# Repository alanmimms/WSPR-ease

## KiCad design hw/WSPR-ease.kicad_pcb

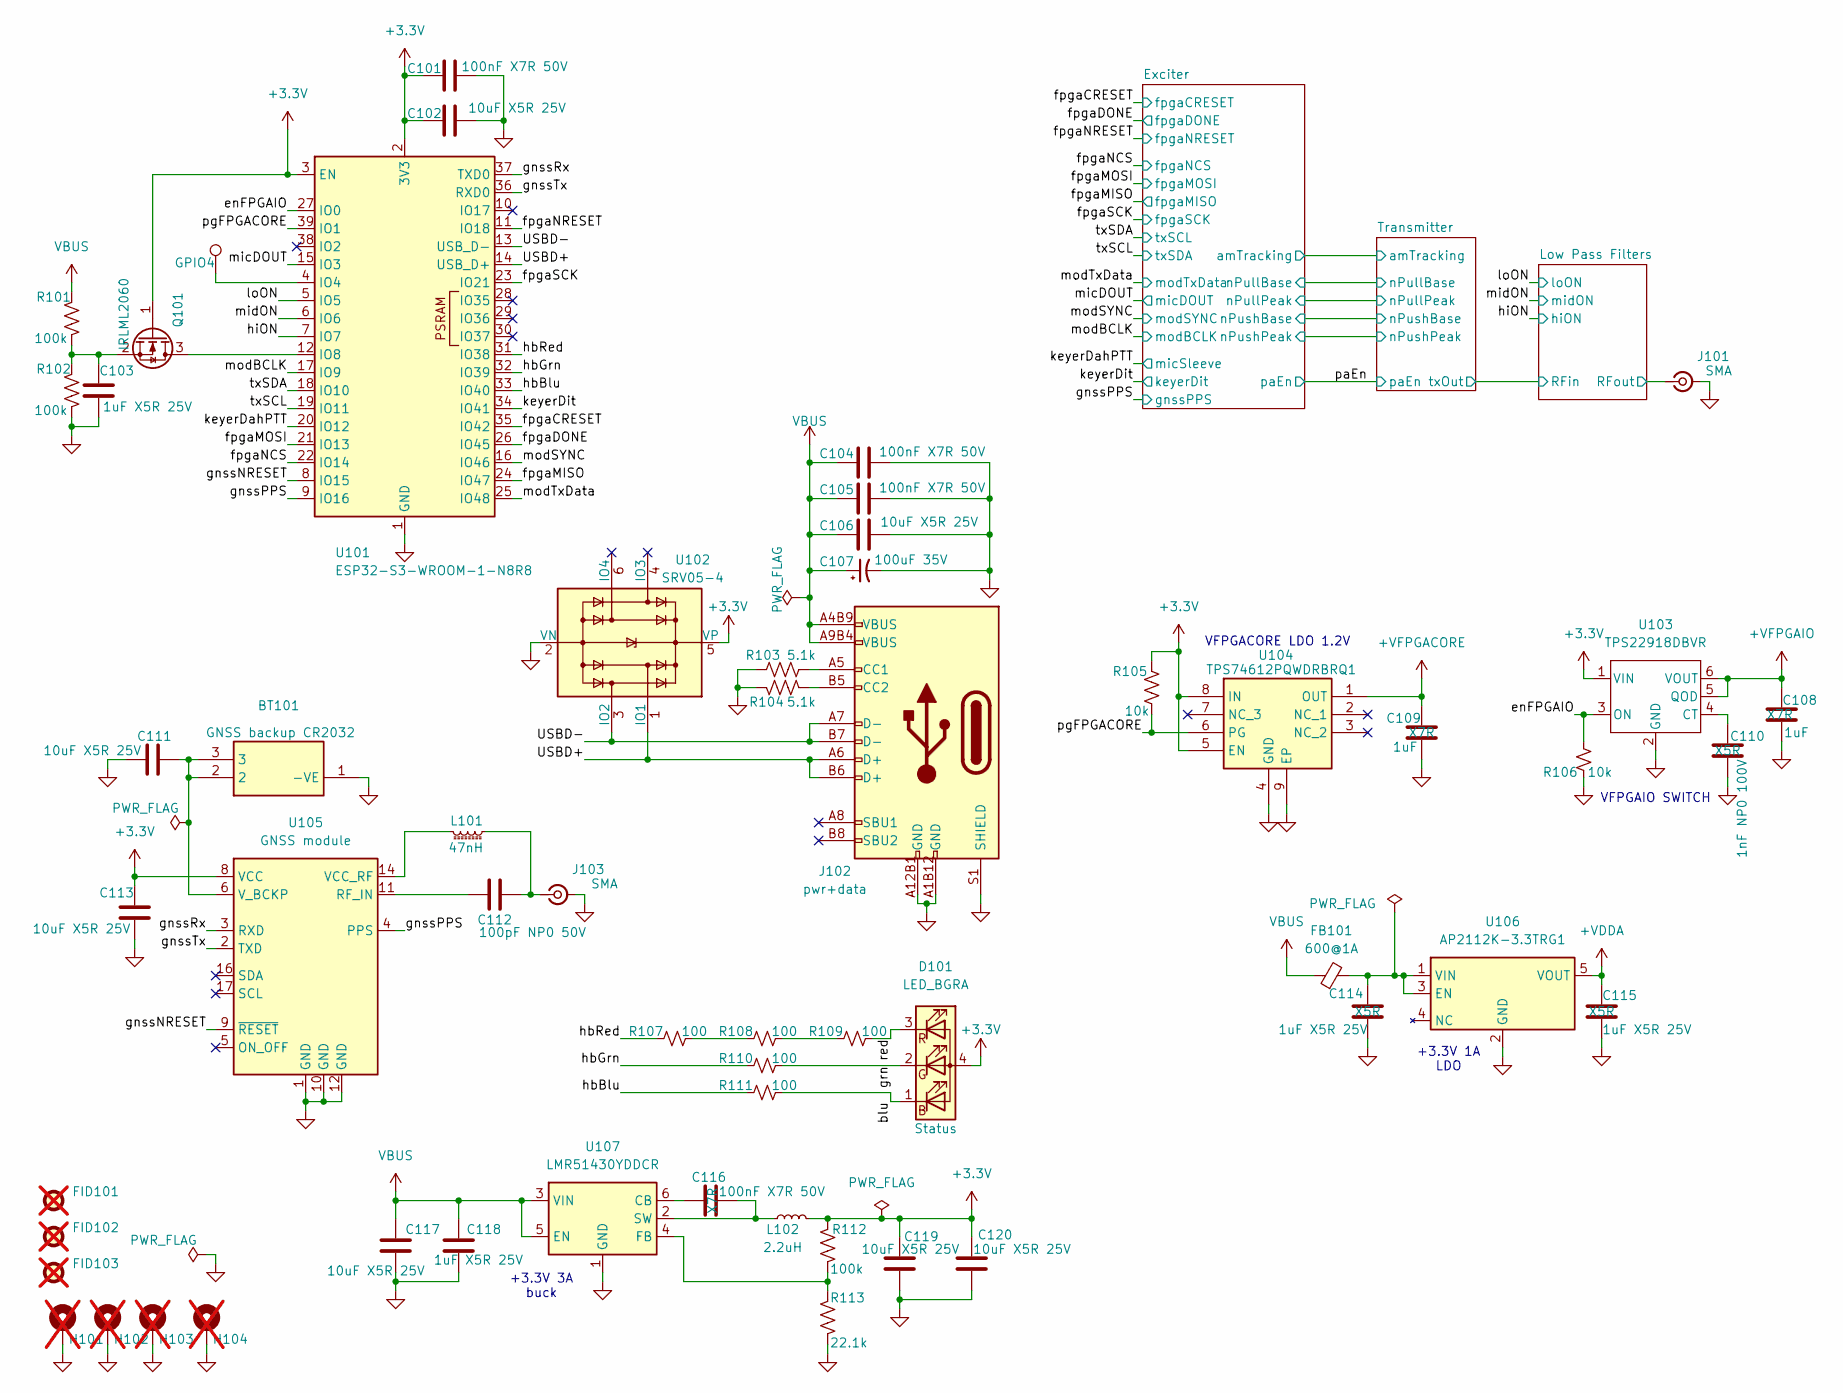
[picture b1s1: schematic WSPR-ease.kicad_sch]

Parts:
BT101: CR3032 holder; S8401-46; Mouser Part Number 855-S8401-46; LCSC C5904513
C101, C104, C105, C116: 100nF X7R 50V; C_0402_1005Metric; MPN KAM05FR71H104KH
C102, C106, C111, C113: 10uF X5R 25V; C_0603_1608Metric; MPN CM105X5R106M25AT; LCSC C479655
C103: 1uF X5R 25V; C_0402_1005Metric; MPN 04023D105MAT2A; LCSC C7393852
C107: 100uF 35V; C_Elec_6.3x7.7; MPN HHXJ350ARA101MF80G; LCSC C46528074
C108, C109: 1uF; C_0402_1005Metric; MPN GRM155Z71A105KE1D; LCSC_PN C301928
C110: 1nF NP0 100V; C_0603_1608Metric; MPN KGM15ACG2A102FT; LCSC_PN C301928
C112: 100pF NP0 50V; C_0402_1005Metric
C114, C115, C118: 1uF X5R 25V; C_0402_1005Metric; MPN 04023D105MAT2A; Mouser_PN 581-04023D105MAT2A
C117: 10uF X5R 25V; C_0603_1608Metric; MPN CM105X5R106M25AT; Mouser_PN 346-CM105X5R106M25AT
C119, C120: 10uF X5R 25V; C_0603_1608Metric; Manufacturer_Part_Number 81-GXT155R71E223KE1D; Mouser Part Number 963-MLAST168BB5106MT
D101: LED_BGRA; UHD111AFKAC3K23E1L3VG5ZB3Z3; MPN UHD111A-FKA-C3K23E1L3VG5ZB3Z3; Mouser_PN 941-UHD1AA3K3E3V53Z3
FB101: 600@1A; L_0603_1608Metric; MPN ILHB0603ER601VHC41; MouserPN 71-ILHB0603E601VHC41
FID101, FID102, FID103: Fiducial; Fiducial_1mm_Mask2mm; LCSC DNP; not fitted
H101, H102, H103, H104: MountingHole_Pad; MountingHole_3.2mm_M3_ISO7380_Pad; LCSC DNP; not fitted
J101, J103: SMA; SMA_Amphenol_901-143_Horizontal; MPN SMA-J-P-H-RA-TH1; LCSC C496551
J102: pwr+data; UJ20-C-H-G-SMT-P16-TR; MPN UJ20-C-H-G-SMT-P16-TR; Mouser_PN 179-UJ20CHGSMTP16TR
L101: 47nH; L_0603_1608Metric; MPN AIMC-0603-47NJ-T; LCSC C98076
L102: 2.2uH; L_1008_2520Metric; MPN APH252010T2R2M; LCSC C5349606
Q101: IRLML2060; SOT-23; MPN IRLML2060TRPBF; Mouser_PN 942-IRLML2060TRPBF
R101, R102: 100k; R_0402_1005Metric; MPN AC0402FR-0747RL; LCSC C2479306
R103, R104: 5.1k; R_0402_1005Metric; MPN MCS04020C5101FE000; Mouser_PN 594-MCS04020C5101FE0
R105: 10k; R_0402_1005Metric; MPN CRT0402-FZ-1003GLF; LCSC_PN C728576
R106: 10k; R_0402_1005Metric; MPN CRT0402-FZ-1003GLF; Mouser_PN 652-CRT0402FZ1003GLF
R107, R108, R109, R110, R111: 100; R_0402_1005Metric; MPN RT0402FRD0722K1L; Mouser_PN 603-RT0402FRD0722K1L
R112: 100k; R_0402_1005Metric; MPN AC0402FR-0747RL; Mouser_PN 603-AC0402FR-0747RL
R113: 22.1k; R_0402_1005Metric; MPN RT0402FRD0722K1L; Mouser_PN 603-RT0402FRD0722K1L
TP101: GPIO4; TestPoint_Pad_1.5x1.5mm
U101: ESP32-S3-WROOM-1-N8R8; ESP32-S3-WROOM-1; Mouser Part Number ESP32-S3-WROOM-1-N8R8; LCSC C2913201
U102: SRV05-4; SOT-23-6; MPN SRV05-4.TCT; LCSC C2836319
U103: TPS22918DBVR; DBV6_TEX; MPN TPS22918DBVR; LCSC_PN C131941
U104: TPS74612PQWDRBRQ1; SON65P300X300X100-9N-D; MPN TPS74612PQWDRBRQ1; LCSC_PN C2868254
U105: GNSS module; ublox_MAX; MPN TESEO-LIV3R; LCSC C5117921
U106: AP2112K-3.3TRG1; SOT95P285X140-5N; Mouser Part Number 621-AP2112K-3.3TRG1
U107: LMR51430YDDCR; SOT-23-6; MPN LMR51430YDDCR; Mouser_PN 595-LMR51430YDDCR

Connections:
+3.3V: C101.1, C102.1, C113.1, C119.1, C120.1, D101.4 (A), L102.2, Q101.1 (G), R105.2, R112.2, U101.2 (3V3), U101.3 (EN), U102.5 (VP), U103.1 (VIN), U104.5 (EN), U104.8 (IN), U105.8 (VCC); also elsewhere on the board
+VDDA: C115.1, U106.5 (VOUT); also elsewhere on the board
+VFPGACORE: C109.1, U104.1 (OUT); also elsewhere on the board
+VFPGAIO: C108.1, U103.5 (QOD), U103.6 (VOUT); also elsewhere on the board
/Low Pass Filters/RFout: J101.1 (In); also elsewhere on the board
/USBD+: J102.A6 (D+), J102.B6 (D+), U101.14 (USB_D+), U102.1 (IO1)
/USBD-: J102.A7 (D-), J102.B7 (D-), U101.13 (USB_D-), U102.3 (IO2)
/blu: D101.1 (BK), R111.2
/enFPGAIO: R106.2, U101.27 (IO0), U103.3 (ON)
/fpgaCRESET: U101.35 (IO42); also elsewhere on the board
/fpgaDONE: U101.26 (IO45); also elsewhere on the board
/fpgaMISO: U101.24 (IO47); also elsewhere on the board
/fpgaMOSI: U101.21 (IO13); also elsewhere on the board
/fpgaNCS: U101.22 (IO14); also elsewhere on the board
/fpgaNRESET: U101.11 (IO18); also elsewhere on the board
/fpgaSCK: U101.23 (IO21); also elsewhere on the board
/gnssNRESET: U101.8 (IO15), U105.9 (~RESET)
/gnssPPS: U101.9 (IO16), U105.4 (PPS); also elsewhere on the board
/gnssRx: U101.37 (TXD0), U105.3 (RXD)
/gnssTx: U101.36 (RXD0), U105.2 (TXD)
/grn: D101.2 (GK), R110.2
/hbBlu: R111.1, U101.33 (IO40)
/hbGrn: R110.1, U101.32 (IO39)
/hbRed: R107.1, U101.31 (IO38)
/hiON: U101.7 (IO7); also elsewhere on the board
/keyerDahPTT: U101.20 (IO12); also elsewhere on the board
/keyerDit: U101.34 (IO41); also elsewhere on the board
/loON: U101.5 (IO5); also elsewhere on the board
/micDOUT: U101.15 (IO3); also elsewhere on the board
/midON: U101.6 (IO6); also elsewhere on the board
/modBCLK: U101.17 (IO9); also elsewhere on the board
/modSYNC: U101.16 (IO46); also elsewhere on the board
/modTxData: U101.25 (IO48); also elsewhere on the board
/pgFPGACORE: R105.1, U101.39 (IO1), U104.6 (PG)
/red: D101.3 (RK), R109.2
/txSCL: U101.19 (IO11); also elsewhere on the board
/txSDA: U101.18 (IO10); also elsewhere on the board
GND: BT101.1 (-VE), C101.2, C102.2, C103.2, C104.2, C105.2, C106.2, C107.2, C108.2, C109.2, C110.2, C111.1, C113.2, C114.2, C115.2, C117.2, C118.2, C119.2, C120.2, H101.1, H102.1, H103.1, H104.1, J101.2 (Ext), J102.A1B12 (GND), J102.A12B1 (GND), J102.S1 (SHIELD), J103.2 (Ext), R102.2, R103.2, R104.2, R106.1, R113.1, U101.1 (GND), U101.40 (GND), U101.41 (GND), U102.2 (VN), U103.2 (GND), U104.4 (GND), U104.9 (EP), U105.1 (GND), U105.10 (GND), U105.12 (GND), U106.2 (GND), U107.1 (GND); also elsewhere on the board
unnamed: J102.A5 (CC1), R103.1
unnamed: J102.B5 (CC2), R104.1
unnamed: C112.2, J103.1 (In), L101.2
unnamed: Q101.3 (D), U101.12 (IO8)
unnamed: C103.1, Q101.2 (S), R101.2, R102.1
unnamed: R107.2, R108.1
unnamed: R108.2, R109.1
unnamed: TP101.1, U101.4 (IO4)
unnamed: C110.1, U103.4 (CT)
unnamed: C112.1, U105.11 (RF_IN)
unnamed: L101.1, U105.14 (VCC_RF)
unnamed: BT101.2, BT101.3, C111.2, U105.6 (V_BCKP)
unnamed: C114.1, FB101.2, U106.1 (VIN), U106.3 (EN)
unnamed: C116.1, U107.6 (CB)
unnamed: R112.1, R113.2, U107.4 (FB)
unnamed: C116.2, L102.1, U107.2 (SW)
VBUS: C104.1, C105.1, C106.1, C107.1, C117.1, C118.1, FB101.1, J102.A4B9 (VBUS), J102.A9B4 (VBUS), R101.1, U107.3 (VIN), U107.5 (EN); also elsewhere on the board

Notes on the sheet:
VFPGAIO SWITCH
+3.3V 1A LDO
+3.3V 3A buck
VFPGACORE LDO 1.2V

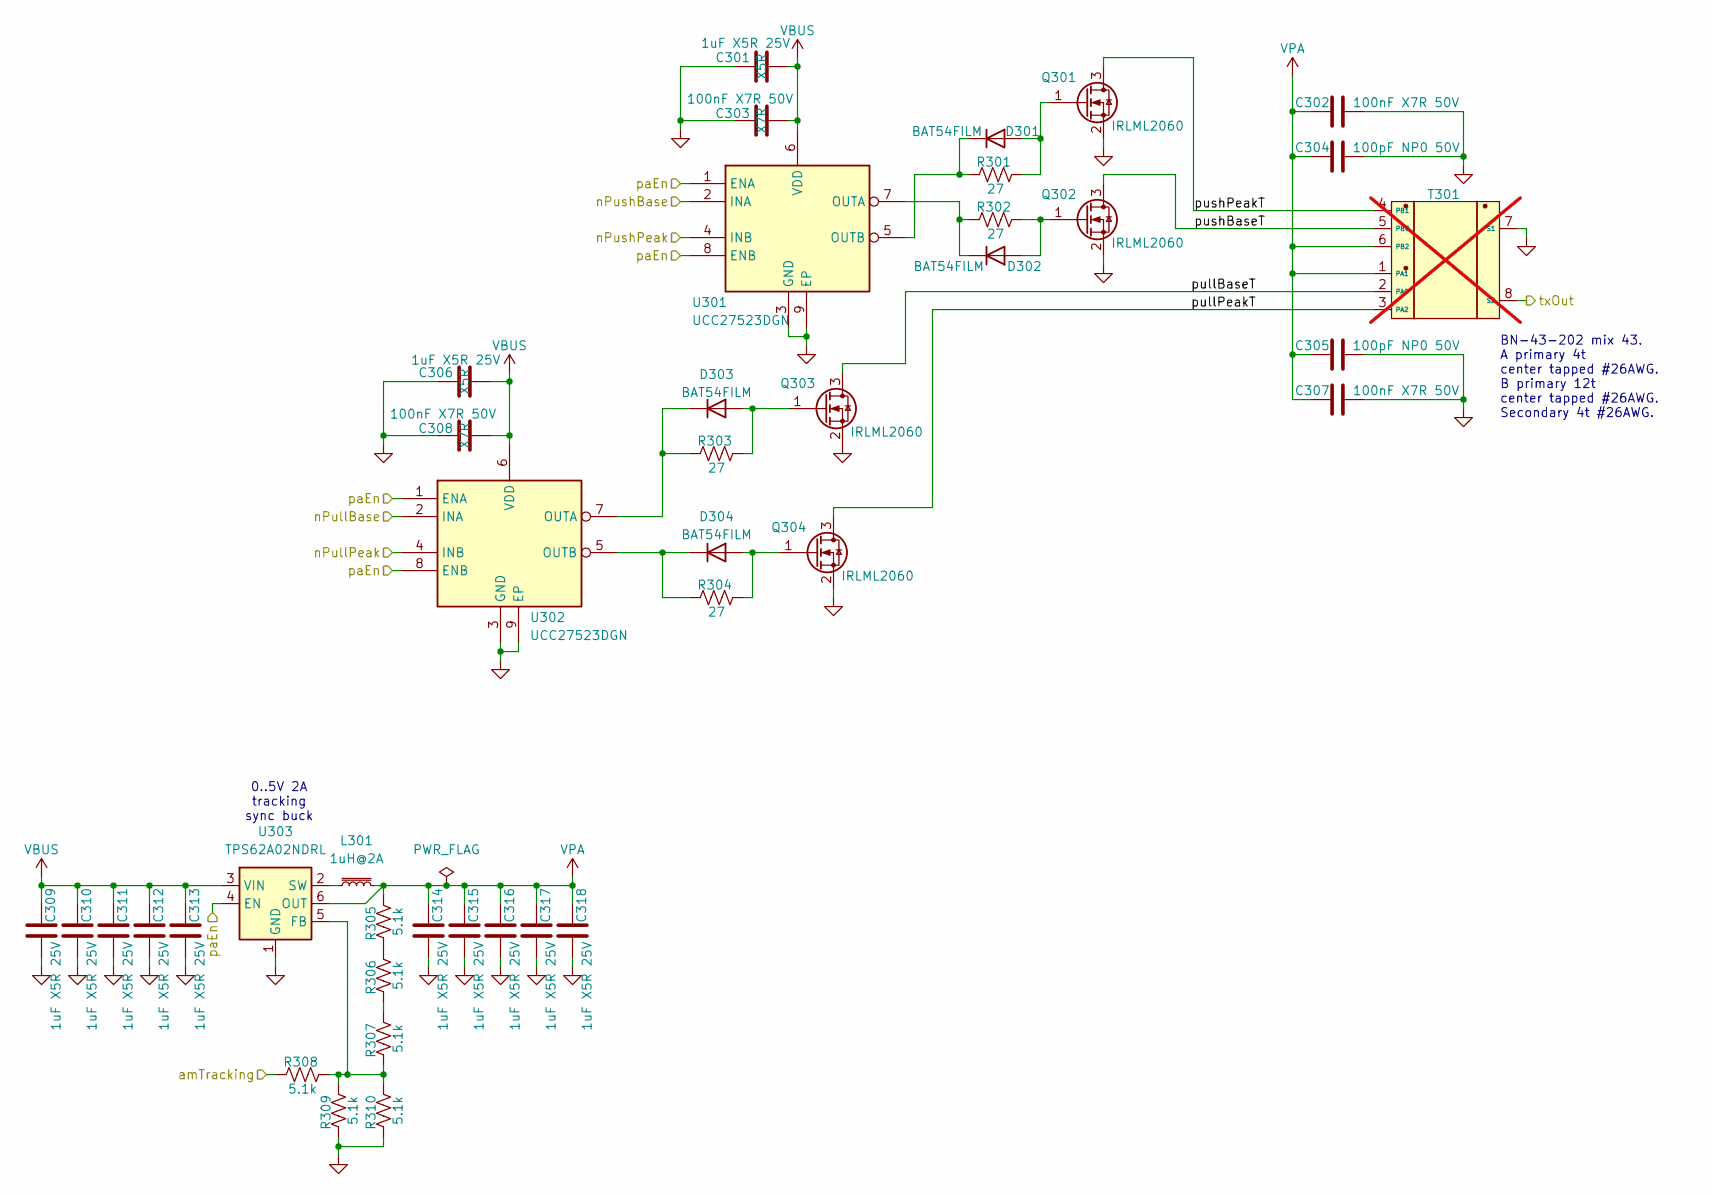
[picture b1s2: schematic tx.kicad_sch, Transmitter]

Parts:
C301, C306: 1uF X5R 25V; C_0402_1005Metric; MPN 04023D105MAT2A; Mouser_PN 581-04023D105MAT2A
C302, C303, C307, C308: 100nF X7R 50V; C_0402_1005Metric; MPN KAM05FR71H104KH
C304, C305: 100pF NP0 50V; C_0402_1005Metric
C309, C310, C311, C312, C313, C314, C315, C316, C317, C318: 1uF X5R 25V; C_0402_1005Metric; MPN 04023D105MAT2A; LCSC C7393852
D301, D302, D303, D304: BAT54FILM; D_SOD-123; MPN BAT54ZFILM; Mouser_PN 511-BAT54FILM
L301: 1uH@2A; PFL4514-inductor; MPN PFL4514-102MEC
Q301, Q302, Q303, Q304: IRLML2060; SOT-23; MPN IRLML2060TRPBF; Mouser_PN 942-IRLML2060TRPBF
R301, R302, R303, R304: 27; R_0402_1005Metric; MPN MCS04020C5101FE000; LCSC C2906874
R305, R306, R307, R308, R309, R310: 5.1k; R_0402_1005Metric
T301: BN-43-202_DualPri_CTSec; bn-43-202-horizontal; MPN 2843000202; LCSC C7174817; not fitted
U301, U302: UCC27523DGN; SOP65P490X110-9N; MPN UCC27525DGNR; Mouser_PN 595-UCC27525DGNR
U303: TPS62A02NDRL; SOT-563

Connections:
/Exciter/amTracking: R308.1; also elsewhere on the board
/Exciter/nPullBase: U302.2 (INA); also elsewhere on the board
/Exciter/nPullPeak: U302.4 (INB); also elsewhere on the board
/Exciter/nPushBase: U301.2 (INA); also elsewhere on the board
/Exciter/nPushPeak: U301.4 (INB); also elsewhere on the board
/Low Pass Filters/RFin: T301.8 (S2); also elsewhere on the board
/Transmitter/pullBaseT: Q303.3 (D), T301.2 (PAC)
/Transmitter/pullPeakT: Q304.3 (D), T301.3 (PA2)
/Transmitter/pushBaseT: Q302.3 (D), T301.5 (PBC)
/Transmitter/pushPeakT: Q301.3 (D), T301.4 (PB1)
/paEn: U301.1 (ENA), U301.8 (ENB), U302.1 (ENA), U302.8 (ENB), U303.4 (EN); also elsewhere on the board
GND: C301.1, C302.2, C303.1, C304.2, C305.2, C306.1, C307.2, C308.1, C309.2, C310.2, C311.2, C312.2, C313.2, C314.2, C315.2, C316.2, C317.2, C318.2, Q301.2 (S), Q302.2 (S), Q303.2 (S), Q304.2 (S), R309.1, R310.1, T301.7 (S1), U301.3 (GND), U301.9 (EP), U302.3 (GND), U302.9 (EP), U303.1 (GND); also elsewhere on the board
unnamed: D301.2 (A), Q301.1 (G), R301.2
unnamed: D301.1 (K), R301.1, U301.5 (OUTB)
unnamed: D302.2 (A), Q302.1 (G), R302.2
unnamed: D302.1 (K), R302.1, U301.7 (OUTA)
unnamed: D303.2 (A), Q303.1 (G), R303.2
unnamed: D303.1 (K), R303.1, U302.7 (OUTA)
unnamed: D304.2 (A), Q304.1 (G), R304.2
unnamed: D304.1 (K), R304.1, U302.5 (OUTB)
unnamed: R305.1, R306.2
unnamed: R306.1, R307.2
unnamed: R307.1, R308.2, R309.2, R310.2, U303.5 (FB)
unnamed: L301.1, U303.2 (SW)
VBUS: C301.2, C303.2, C306.2, C308.2, C309.1, C310.1, C311.1, C312.1, C313.1, U301.6 (VDD), U302.6 (VDD), U303.3 (VIN); also elsewhere on the board
VPA: C302.1, C304.1, C305.1, C307.1, C314.1, C315.1, C316.1, C317.1, C318.1, L301.2, R305.2, T301.1 (PA1), T301.6 (PB2), U303.6 (OUT)

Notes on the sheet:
BN-43-202 mix 43. A primary 4t center tapped #26AWG. B primary 12t center tapped #26AWG. Secondary 4t #26AWG.
0..5V 2A tracking sync buck

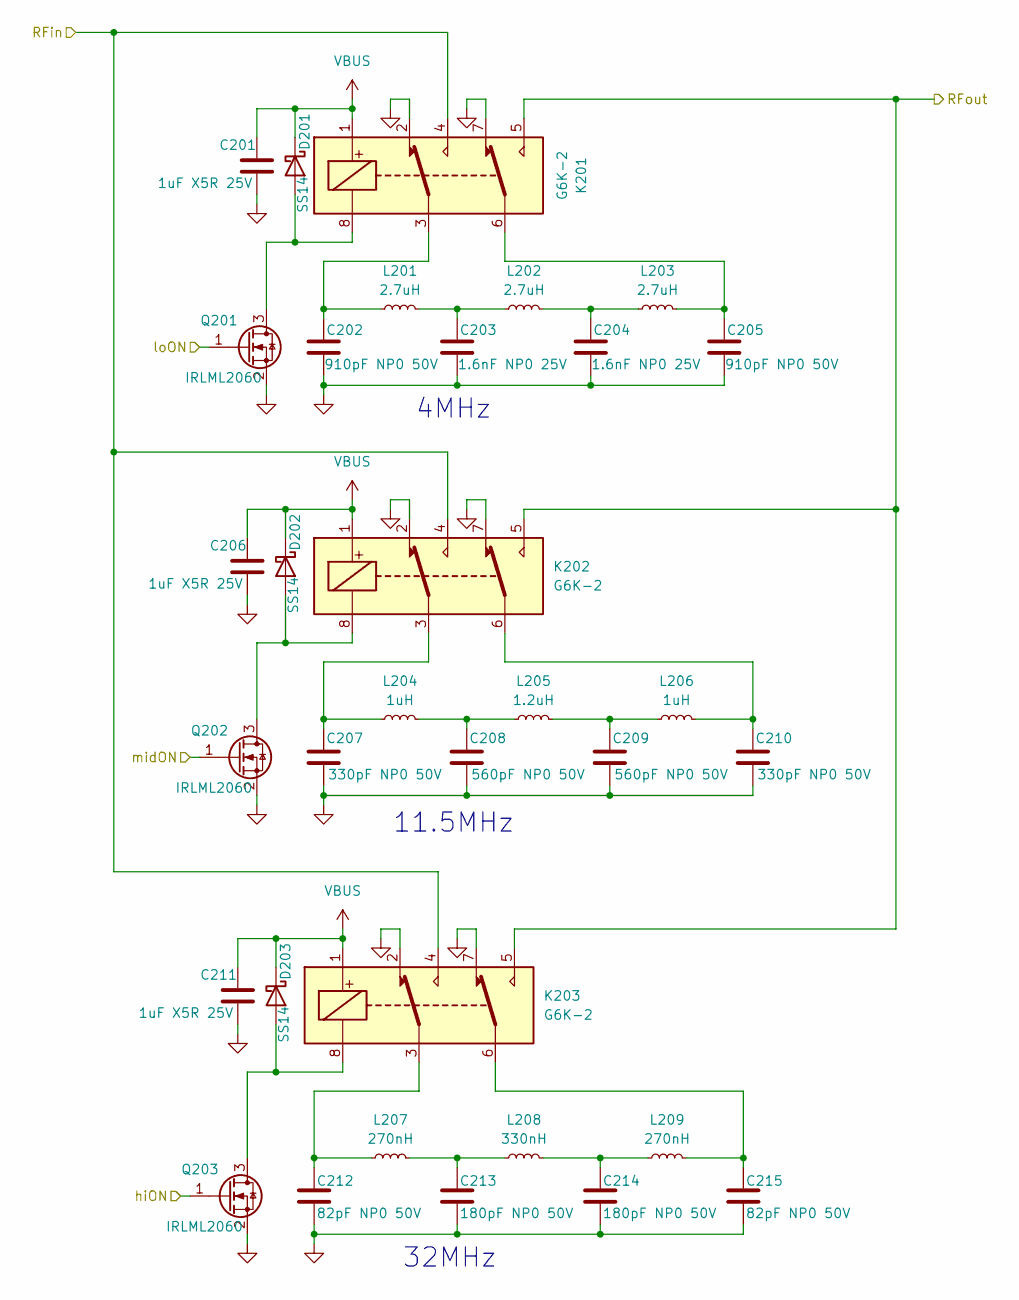
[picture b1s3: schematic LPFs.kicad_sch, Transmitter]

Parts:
C201, C206, C211: 1uF X5R 25V; C_0402_1005Metric; MPN 04023D105MAT2A; LCSC C7393852
C202, C205: 910pF NP0 50V; C_0402_1005Metric
C203, C204: 1.6nF NP0 25V; C_0402_1005Metric
C207, C210: 330pF NP0 50V; C_0402_1005Metric
C208, C209: 560pF NP0 50V; C_0402_1005Metric
C212, C215: 82pF NP0 50V; C_0402_1005Metric
C213, C214: 180pF NP0 50V; C_0402_1005Metric
D201, D202, D203: SS14; D_SMA; MPN SS14; LCSC C45406502
K201, K202, K203: G6K-2; Relay_DPDT_Omron_G6K-2G; MPN G6K-2G-DC5; Mouser_PN 653-G6K-2G-DC5
L201, L202, L203: 2.7uH; L_1008_2520Metric; MPN 1008LS-272XJRC; Mouser_PN 994-1008LS-272XJRC
L204, L206: 1uH; L_1008_2520Metric; MPN 1008CS-102XJRC; Mouser_PN 994-1008CS-102XJRC
L205: 1.2uH; L_1008_2520Metric; MPN 1008CS-122XJRC; Mouser_PN 994-1008CS-122XJRC
L207, L209: 270nH; L_0805_2012Metric; MPN 1008CS-271XGRC; LCSC C48946576
L208: 330nH; L_0805_2012Metric; MPN 1008CS-331XGRC; LCSC C48946577
Q201, Q202, Q203: IRLML2060; SOT-23; MPN IRLML2060TRPBF; Mouser_PN 942-IRLML2060TRPBF

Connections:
/Low Pass Filters/RFin: K201.4, K202.4, K203.4; also elsewhere on the board
/Low Pass Filters/RFout: K201.5, K202.5, K203.5; also elsewhere on the board
/hiON: Q203.1 (G); also elsewhere on the board
/loON: Q201.1 (G); also elsewhere on the board
/midON: Q202.1 (G); also elsewhere on the board
GND: C201.2, C202.2, C203.2, C204.2, C205.2, C206.2, C207.2, C208.2, C209.2, C210.2, C211.2, C212.2, C213.2, C214.2, C215.2, K201.2, K201.7, K202.2, K202.7, K203.2, K203.7, Q201.2 (S), Q202.2 (S), Q203.2 (S); also elsewhere on the board
unnamed: C202.1, K201.3, L201.1
unnamed: C203.1, L201.2, L202.1
unnamed: C204.1, L202.2, L203.1
unnamed: C205.1, K201.6, L203.2
unnamed: C207.1, K202.3, L204.1
unnamed: C208.1, L204.2, L205.1
unnamed: C209.1, L205.2, L206.1
unnamed: C210.1, K202.6, L206.2
unnamed: C212.1, K203.3, L207.1
unnamed: C213.1, L207.2, L208.1
unnamed: C214.1, L208.2, L209.1
unnamed: C215.1, K203.6, L209.2
unnamed: D201.2 (A), K201.8, Q201.3 (D)
unnamed: D202.2 (A), K202.8, Q202.3 (D)
unnamed: D203.2 (A), K203.8, Q203.3 (D)
VBUS: C201.1, C206.1, C211.1, D201.1 (K), D202.1 (K), D203.1 (K), K201.1, K202.1, K203.1; also elsewhere on the board

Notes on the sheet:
4MHz
32MHz
11.5MHz

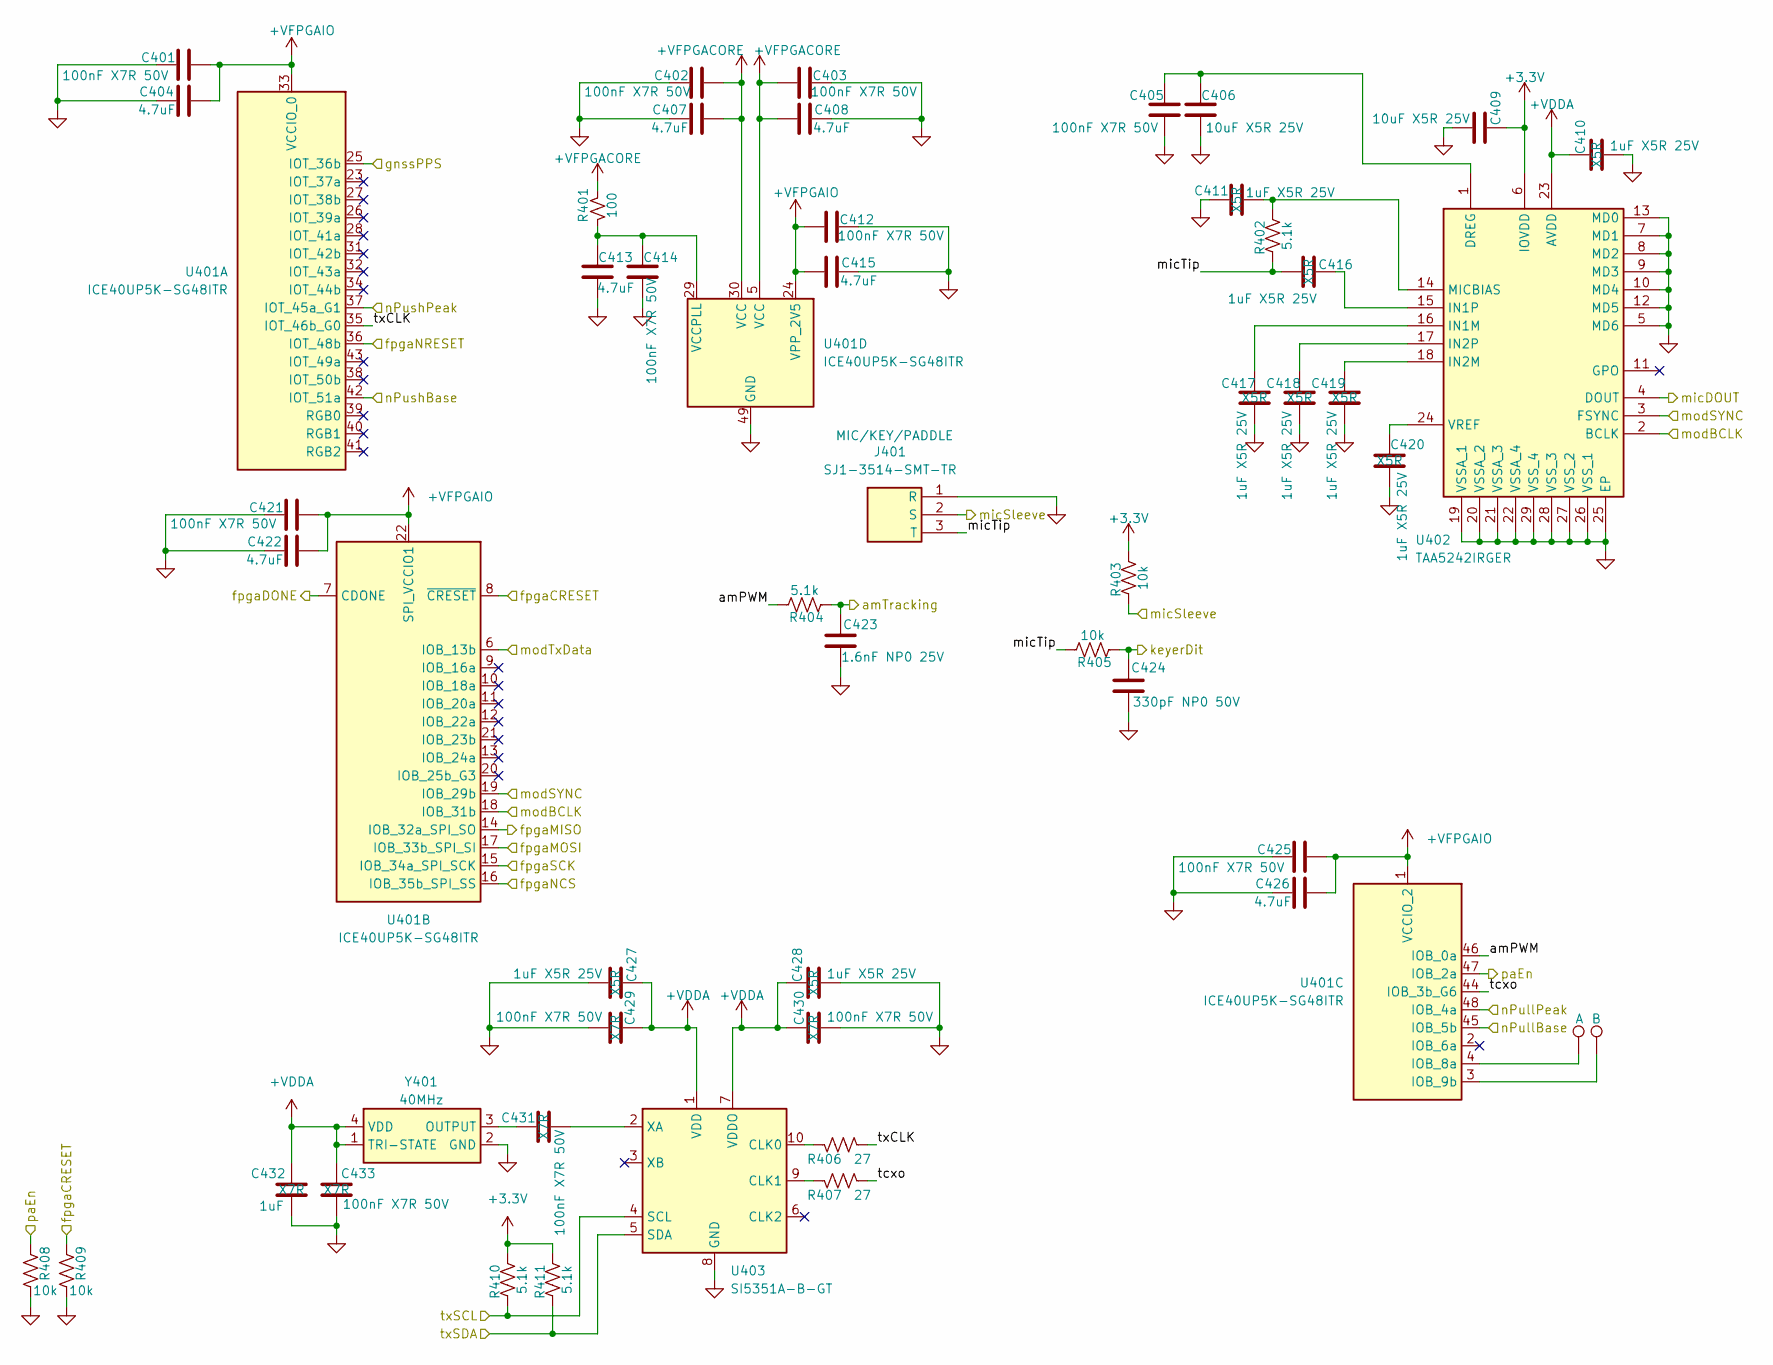
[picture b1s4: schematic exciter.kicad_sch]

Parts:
C401, C402, C403, C405, C412, C414, C421, C425: 100nF X7R 50V; C_0402_1005Metric; MPN KGM15BR71H104KT; LCSC C24452
C404, C407, C408, C413, C415, C422, C426: 4.7uF; C_0402_1005Metric; MPN CM05X5R475M10AH; LCSC_PN C18535241
C406: 10uF X5R 25V; C_0603_1608Metric; Manufacturer_Part_Number 81-GXT155R71E223KE1D; Mouser Part Number 963-MLAST168BB5106MT
C409: 10uF X5R 25V; C_0603_1608Metric; MPN CM105X5R106M25AT; LCSC C96446
C410, C411, C416, C417, C418, C419, C420, C427, C428: 1uF X5R 25V; C_0402_1005Metric; MPN 04023D105MAT2A; Mouser_PN 581-04023D105MAT2A
C423: 1.6nF NP0 25V; C_0402_1005Metric
C424: 330pF NP0 50V; C_0402_1005Metric
C429, C430, C431: 100nF X7R 50V; C_0402_1005Metric; MPN KAM05FR71H104KH
C432: 1uF; C_0402_1005Metric; MPN GRM155Z71A105KE1D; LCSC_PN C301928
C433: 100nF X7R 50V; C_0402_1005Metric; MPN KGM15BR71H104KT; LCSC_PN C24452
J401: SJ1-3514-SMT-TR; 35RASMT2BHWNTRX; Mouser Part Number 502-35RASMT2BHWNTRX
R401: 100; R_0402_1005Metric; MPN RT0402FRD0722K1L; Mouser_PN 603-RT0402FRD0722K1L
R402, R404: 5.1k; R_0402_1005Metric; MPN MCT06030C1009FP500; LCSC C2907091
R403, R405: 10k; R_0402_1005Metric; MPN MCT06030C1009FP500; LCSC C2907091
R406, R407: 27; R_0402_1005Metric; MPN MCS04020C5101FE000; Mouser_PN 594-MCS04020C5101FE0
R408, R409: 10k; R_0402_1005Metric; MPN CRT0402-FZ-1003GLF; LCSC C60490
R410, R411: 5.1k; R_0402_1005Metric; MPN MCS04020C5101FE000; LCSC C2906874
TP401: A; TestPoint_Pad_1.5x1.5mm
TP402: B; TestPoint_Pad_1.5x1.5mm
U401: ICE40UP5K-SG48ITR; QFN50P700X700X100-49N-D; MPN ICE40UP5K-SG48I; LCSC C2678152
U402: TAA5242IRGER; Manufacturer_Part_Number TAA5242IRGER
U403: SI5351A-B-GT; MSOP-10_3x3mm_P0.5mm; MPN SI5351C-B-GM1; Mouser_PN 634-SI5351C-B-GM1
Y401: 40MHz; ECSTXO201633400TR; MPN ECS-TXO-2016-33-400-TR; LCSC_PN C2451471

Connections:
+3.3V: C409.2, R403.2, R410.2, R411.2, U402.6 (IOVDD); also elsewhere on the board
+VDDA: C410.1, C427.1, C428.1, C429.2, C430.2, C432.1, C433.1, U402.23 (AVDD), U403.1 (VDD), U403.7 (VDDO), Y401.1 (TRI-STATE), Y401.4 (VDD); also elsewhere on the board
+VFPGACORE: C402.2, C403.2, C407.1, C408.1, R401.2, U401.5 (VCC), U401.30 (VCC); also elsewhere on the board
+VFPGAIO: C401.2, C404.1, C412.2, C415.1, C421.2, C422.1, C425.2, C426.1, U401.1 (VCCIO_2), U401.22 (SPI_VCCIO1), U401.24 (VPP_2V5), U401.33 (VCCIO_0); also elsewhere on the board
/Exciter/amPWM: R404.2, U401.46 (IOB_0a)
/Exciter/amTracking: C423.1, R404.1; also elsewhere on the board
/Exciter/micTip: C416.2, J401.3 (T), R402.1, R405.2
/Exciter/nPullBase: U401.45 (IOB_5b); also elsewhere on the board
/Exciter/nPullPeak: U401.48 (IOB_4a); also elsewhere on the board
/Exciter/nPushBase: U401.42 (IOT_51a); also elsewhere on the board
/Exciter/nPushPeak: U401.37 (IOT_45a_G1); also elsewhere on the board
/Exciter/tcxo: R407.1, U401.44 (IOB_3b_G6)
/Exciter/txCLK: R406.1, U401.35 (IOT_46b_G0)
/fpgaCRESET: R409.1, U401.8 (~CRESET); also elsewhere on the board
/fpgaDONE: U401.7 (CDONE); also elsewhere on the board
/fpgaMISO: U401.14 (IOB_32a_SPI_SO); also elsewhere on the board
/fpgaMOSI: U401.17 (IOB_33b_SPI_SI); also elsewhere on the board
/fpgaNCS: U401.16 (IOB_35b_SPI_SS); also elsewhere on the board
/fpgaNRESET: U401.36 (IOT_48b); also elsewhere on the board
/fpgaSCK: U401.15 (IOB_34a_SPI_SCK); also elsewhere on the board
/gnssPPS: U401.25 (IOT_36b); also elsewhere on the board
/keyerDahPTT: J401.2 (S), R403.1; also elsewhere on the board
/keyerDit: C424.1, R405.1; also elsewhere on the board
/micDOUT: U402.4 (DOUT); also elsewhere on the board
/modBCLK: U401.18 (IOB_31b), U402.2 (BCLK); also elsewhere on the board
/modSYNC: U401.19 (IOB_29b), U402.3 (FSYNC); also elsewhere on the board
/modTxData: U401.6 (IOB_13b); also elsewhere on the board
/paEn: R408.1, U401.47 (IOB_2a); also elsewhere on the board
/txSCL: R411.1, U403.5 (SDA); also elsewhere on the board
/txSDA: R410.1, U403.4 (SCL); also elsewhere on the board
GND: C401.1, C402.1, C403.1, C404.2, C405.1, C406.1, C407.2, C408.2, C409.1, C410.2, C411.2, C412.1, C413.2, C414.1, C415.2, C417.2, C418.2, C419.2, C420.2, C421.1, C422.2, C423.2, C424.2, C425.1, C426.2, C427.2, C428.2, C429.1, C430.1, C432.2, C433.2, J401.1 (R), R408.2, R409.2, U401.49 (GND), U402.5 (MD6), U402.7 (MD1), U402.8 (MD2), U402.9 (MD3), U402.10 (MD4), U402.12 (MD5), U402.13 (MD0), U402.19 (VSSA_1), U402.20 (VSSA_2), U402.21 (VSSA_3), U402.22 (VSSA_4), U402.25 (EP), U402.26 (VSS_1), U402.27 (VSS_2), U402.28 (VSS_3), U402.29 (VSS_4), U403.8 (GND), Y401.2 (GND); also elsewhere on the board
unnamed: TP401.1, U401.4 (IOB_8a)
unnamed: TP402.1, U401.3 (IOB_9b)
unnamed: C413.1, C414.2, R401.1, U401.29 (VCCPLL)
unnamed: C405.2, C406.2, U402.1 (DREG)
unnamed: C417.1, U402.16 (IN1M)
unnamed: C416.1, U402.15 (IN1P)
unnamed: C419.1, U402.18 (IN2M)
unnamed: C418.1, U402.17 (IN2P)
unnamed: C411.1, R402.2, U402.14 (MICBIAS)
unnamed: C420.1, U402.24 (VREF)
unnamed: R406.2, U403.10 (CLK0)
unnamed: R407.2, U403.9 (CLK1)
unnamed: C431.2, U403.2 (XA)
unnamed: C431.1, Y401.3 (OUTPUT)

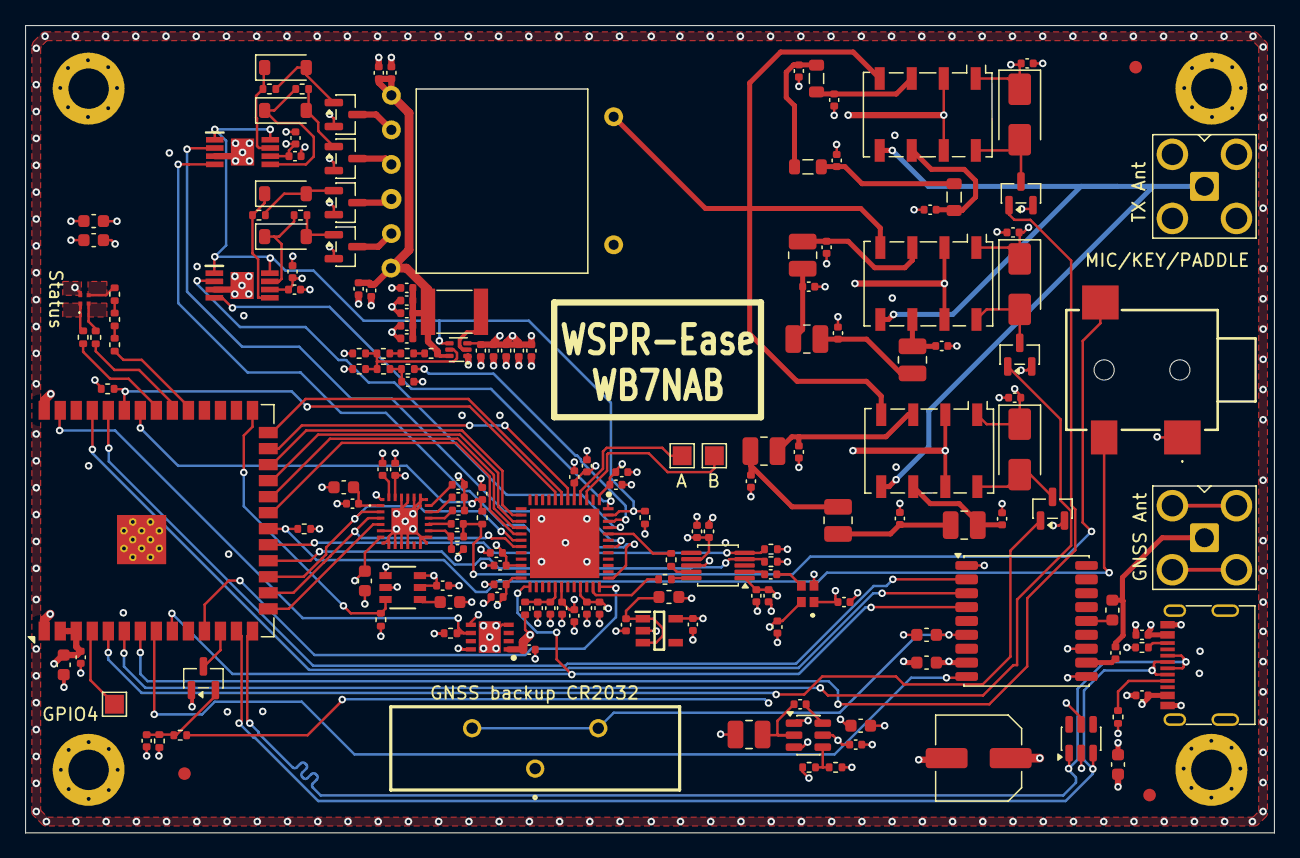
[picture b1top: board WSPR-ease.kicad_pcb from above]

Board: 4 copper layers, 99.0 x 64.0 mm, 182 parts (0 on the bottom side), 112 nets.

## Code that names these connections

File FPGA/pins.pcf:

# Clock Inputs
set_io txCLK 35
set_io tcxo 44
set_io gnssPPS 25

# SPI Interface
set_io fpgaMISO 14
set_io fpgaSCK 15
set_io fpgaNCS 16
set_io fpgaMOSI 17

# I2S Audio Bus Inputs (from ESP32, BCLK/SYNC shared with mic ADC)
set_io modTxData 6
set_io modBCLK 18
set_io modSYNC 19

# RF Exciter & Control Outputs
set_io rfPushPeak 37
set_io rfPushBase 42
set_io rfPullPeak 48
set_io rfPullBase 45
set_io paEn 47
set_io amPWM 46

# Debug Pads
set_io padA 4
set_io padB 3

# Reset without reconfiguration
set_io fpgaNRESET 36

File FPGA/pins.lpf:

# WSPR-ease CPLD Pin Constraints
# Device: LCMXO2-256HC-4SG32C (32-pin QFN/TQFP)

LOCATE COMP "rf_clk_pin" SITE "21";     # PCLKT1_0 (modulated clock from Si5351 CLK0)
LOCATE COMP "pwm_clk_pin" SITE "4";      # PCLKT3_0 (PWM rate clock from Si5351 CLK2)
LOCATE COMP "pwm_out" SITE "5";          # PCLKC3_0 (PWM output driving RC filter)
LOCATE COMP "nPullPeak" SITE "11";       # PCLKT2_0 (active-low gate output)
LOCATE COMP "nPullBase" SITE "12";       # PCLKC2_0 (active-low gate output)
LOCATE COMP "nPushPeak" SITE "13";       # PCLKT2_1 (active-low gate output)
LOCATE COMP "nPushBase" SITE "14";       # PCLKC2_1 (active-low gate output)
LOCATE COMP "fpgaNCS" SITE "8";          # SPI CS
LOCATE COMP "fpgaMOSI" SITE "17";        # SPI MOSI
LOCATE COMP "fpgaMISO" SITE "10";        # SPI MISO
LOCATE COMP "fpgaSCLKpin" SITE "9";      # SPI SCK (Clock)

IOBUF PORT "rf_clk_pin" IO_TYPE=LVCMOS33PULLMODE=NONE;
IOBUF PORT "pwm_clk_pin" IO_TYPE=LVCMOS33PULLMODE=NONE;
IOBUF PORT "pwm_out" IO_TYPE=LVCMOS33 SLEWRATE=FAST DRIVE=8;
IOBUF PORT "nPullPeak" IO_TYPE=LVCMOS33 SLEWRATE=FAST DRIVE=8;
IOBUF PORT "nPullBase" IO_TYPE=LVCMOS33 SLEWRATE=FAST DRIVE=8;
IOBUF PORT "nPushPeak" IO_TYPE=LVCMOS33 SLEWRATE=FAST DRIVE=8;
IOBUF PORT "nPushBase" IO_TYPE=LVCMOS33 SLEWRATE=FAST DRIVE=8;
IOBUF PORT "fpgaNCS" IO_TYPE=LVCMOS33 PULLMODE=UP;
IOBUF PORT "fpgaMOSI" IO_TYPE=LVCMOS33 PULLMODE=NONE;
IOBUF PORT "fpgaMISO" IO_TYPE=LVCMOS33 SLEWRATE=FAST DRIVE=8;
IOBUF PORT "fpgaSCLKpin" IO_TYPE=LVCMOS33 PULLMODE=NONE;

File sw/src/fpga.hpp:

/*
 * CPLD/FPGA Control Module for WSPR-ease
 * Handles CPLD interaction, Si5351 clock initialization, and SPI register updates.
 */

#pragma once

#include <cstdint>
#include "Si5351.hpp"

namespace wspr {

  enum class WSPRBand : uint32_t {
    Band160m = 1836600,
    Band80m  = 3568600,
    Band60m  = 5287200,
    Band40m  = 7038600,
    Band30m  = 10138700,
    Band20m  = 14095600,
    Band17m  = 18104600,
    Band15m  = 21094600,
    Band12m  = 24924600,
    Band10m  = 28124600,
    Band6m   = 50293000,
  };

  class FPGA {
  public:
    static FPGA& instance();

    static const unsigned tcxoFreqHz = 20 * 1000 * 1000; // 20 MHz TCXO reference for Si5351

    int init();
    int reset();
    int loadBitstream(const char* path);

    // Frequency control (CLK0 outputs 6x this frequency)
    int setFrequency(uint32_t freq_hz);
    uint32_t frequency() const { return currentFreq; }

    // Transmission control
    int startTX();
    int stopTX();
    bool isTransmitting() const { return initialized && transmitting; }

    // Send WSPR symbol (0-3) - 4-FSK modulation
    int sendSymbol(uint8_t symbol);

    // LPF band switching (controlled by loON, midON, hiON GPIOs)
    int setLPFBand(WSPRBand band);
    WSPRBand getBand() const { return currentBand; }

    // Atomic Polar Modulation update for AM, SSB, and CW envelope
    int updatePolarMod(uint16_t amplitude, uint16_t phase);

    // Soft reset trigger for internal CPLD state machines
    int triggerSoftReset(bool assertReset);

    // Raw register access for diagnostics
    int readRegister(uint8_t reg, uint32_t* value) { return spiReadReg(reg, value); }
    int writeRegister(uint8_t reg, uint32_t value) { return spiWriteReg(reg, value); }

    bool isInitialized() const { return initialized; }

    // Reference to Si5351 instance
    Si5351& getSi5351() { return si5351; }

  private:
    FPGA() = default;

    int spiWriteReg(uint8_t reg, uint32_t value);
    int spiReadReg(uint8_t reg, uint32_t* value);

    bool initialized = false;
    bool transmitting = false;
    uint32_t currentFreq = 0;
    WSPRBand currentBand = WSPRBand::Band20m;

    Si5351 si5351;
  };

} // namespace wspr

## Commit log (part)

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2026-04-13 1-2-1 last rites?
2026-04-13 Actually this might be last 1-2-1 version instead
2026-04-16 Use relays and do layout over again to make these damned things fit
2026-04-16 Timing closure at ~87MHz with DSP mutiplier approach and cosim. We will work on adding margin to timing next. I have not tested on hw yet.
2026-04-16 lose this big file
2026-04-16 OK timing closes at 90MHz
2026-04-16 Add a command line I use so I can figure this out in future coming back after time
2026-04-16 Timing now closes at 121MHz. But output still does not produce any signal on my scope. Shit.
2026-04-16 Update documentation to match where we are now with FPGA
2026-04-17 Use VFPGAIO for pullup for driverNEN. Fix some layout issues with more equal routing lengths in critical tx phase paths.
2026-04-17 Timing closure, but still no signal on pull2
2026-04-18 Now generating some pull2 transitions at proper freq (not proper width). Co-sim is verifying Lattice hard macro functions in functional sim meant to emulate these since this lack has been a blind are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
2026-04-18 These did not work.
2026-04-18 Remove power setting API
2026-04-20 Checkpoint before switching AI strategies
2026-04-20 Fix FPGA phase breathing: align pipeline and increase dither amplitude
2026-04-20 Getting closer, but still BREATHING
2026-05-07 Add env setup
2026-05-07 Add more instructions to build
2026-05-08 Prep to move entirely to amaranth for FPGA RTL
2026-05-08 Checkpoint before revamping testbench - now broken for SPI
2026-05-08 Checkpoint after rewrite in amaranth. Still not generating wave output nor is SPI working, but it is progress
2026-05-09 still not outputting waveform. will try again tomorrow
2026-05-10 FPGA: Implement zero-fabric-carry DSP NCO and achieve 94MHz timing closure
    - Refactored 48-bit PipelinedNCO to use 3 pipelined SB_MAC16 DSP blocks,
    eliminating all fabric carry-chain bottlenecks.
    - Migrated FrequencyCounter to the 8th DSP block for 32-bit precision at speed.
    - Overhauled SPIRegisters with one-hot address decoding and registered data
    fetching to resolve massive cross-chip routing delays.
    - Resolved posedge-to-negedge half-cycle IO timing violations by registering
2026-05-10 FPGA: Fix pipeline misalignment in Exciter and update test bench for 1-2-1 modulation
2026-05-10 Rename symbols so I can read the code
2026-05-10 Convert LaTeX math escapes to UTF-8 characters
2026-05-12 Rename files to match new naming
2026-05-13 Eliminate more evil underscores. Still debugging FPGA spurious random pulse problem.
2026-05-13 Getting ready to make sim based on parameterized and DRY centralized timing rather than copypasta hackware AI created.
2026-05-13 Clean up a lot. Switch to common clocking for sim rather than a buncha copypasta everywhere, 90MHz clock
2026-05-14 Use Top.v with no wrapper in sim again. Try another seed to time.
2026-05-14 Add some debug for sim. Fix offs module to do actual 16-bit add with right params.
2026-05-15 No longer have "sim" make target
2026-06-09 Convert to async based sim. Sort 90MHz vs 40MHz clocking and use SB_PLL40_PAD to generate both. Clean up sim vs hw build to create two separate RTL outputs from Amaranth gateware.py. Probably this st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
2026-06-09 Lose old gen dir
2026-06-09 Sim is running a little now with new C++20 async stuff.
2026-06-09 Fix RF exciter pin phase alignment, state 6 clamping, and square wave mode pin assignments; timing closed at 100.93MHz
2026-06-09 Eliminate negative-edge clocking in fabric, move FPGACommon to header-only, and verify builds
2026-06-09 Add build number register and verification in sim and firmware
2026-06-09 Keep buildNumber.txt in git so it keeps going up (multiple clones will cause problems!). Starting to figure out why hw DDR IO is generating the wrong signals but still borked.
2026-06-10 Set DDR pin type to no enable no register DDR, unset clock and enable pins. This did not change a thing in the result.
2026-06-10 Align rising/falling edge delays, fix cells_sim.v simulation fidelity, and resolve Makefile dependency caching
2026-06-10 Fix 90MHz hardware toggling by replacing DSP adder/multipliers in Exciter with fabric logic
2026-06-10 Fix simulation/hardware DDR mapping discrepancy and align pipeline delays
2026-06-10 Make this match the iCE40UP FPGA reality
2026-06-10 Closer. I think the LFSR dithering is causing problems now since I reenabled it.
2026-06-13 I think this is now using the SB_MAC16 properly for each instance. The AI based configs were all screwed up. I listed teh name from the iCE40 Tech Lib doc for each flavor used in a comment to help if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
2026-06-18 Fix SB_MAC16 in NCO to use UPPER 16-bits of result since A is mapped to the top half.
2026-06-18 Fix FreqCounter SB_MAC16 config (but not yet tested)
2026-06-18 Fixed up macR multiplier - still not 100%, but I think this is "closer"
2026-06-19 Now it seems I am multiplying properly in the exciter
2026-06-19 Fix routing problem for multiplier resets
2026-06-19 Add original recipe code for cells_sim.v in case we need to revert. Changed the bit shift for the dithering noise to make it less jittery. I think it is generating 9MHz and lower quite well now.
2026-06-19 Add 0MHz "tx stop" equivalent. Fix DOS line endings.
2026-06-20 Fucking USB 16-pin footprint! Also, completely redid the layout and wiring of the transmitter using a MOSFET gate and R+diode gate drive, simplify BOM, enhance LPFs for square wave output >= 10MHz.
2026-06-20 Close timing again. Sigh.
2026-06-21 Checkpoint after significant refactoring which BROKE the FPGA
2026-06-22 Add VERILATOR macro condition for evil tristate it does not support
2026-06-22 The square wave and 1-2-1 modulation are properly dithering now. When I move to UCC27524DGN gate driver and 10R+1N4148 diode on the gate drive, I think the shoot-through will mostly disappear. I cann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
2026-06-24 FPGA last rites
2026-06-26 Add symbols for new components, switch to SI5351 in place of FPGA. Simplify!
2026-06-26 Add footprints too
2026-06-26 Switch to SI5351C-B-GM for exciter + AHC to attenuate 3rd harmonic on a separate winding on the binocular transformer. Do so layout tweaks. This is much simpler than the FPGA version.
2026-06-27 Horsing around with JLCPCB assembly and BOM. I think it is still too expensive to do it this way for p1 build
2026-06-27 OCD fixes. Fix USB2 connector footprint AGAIN (these things are not standardized!).
